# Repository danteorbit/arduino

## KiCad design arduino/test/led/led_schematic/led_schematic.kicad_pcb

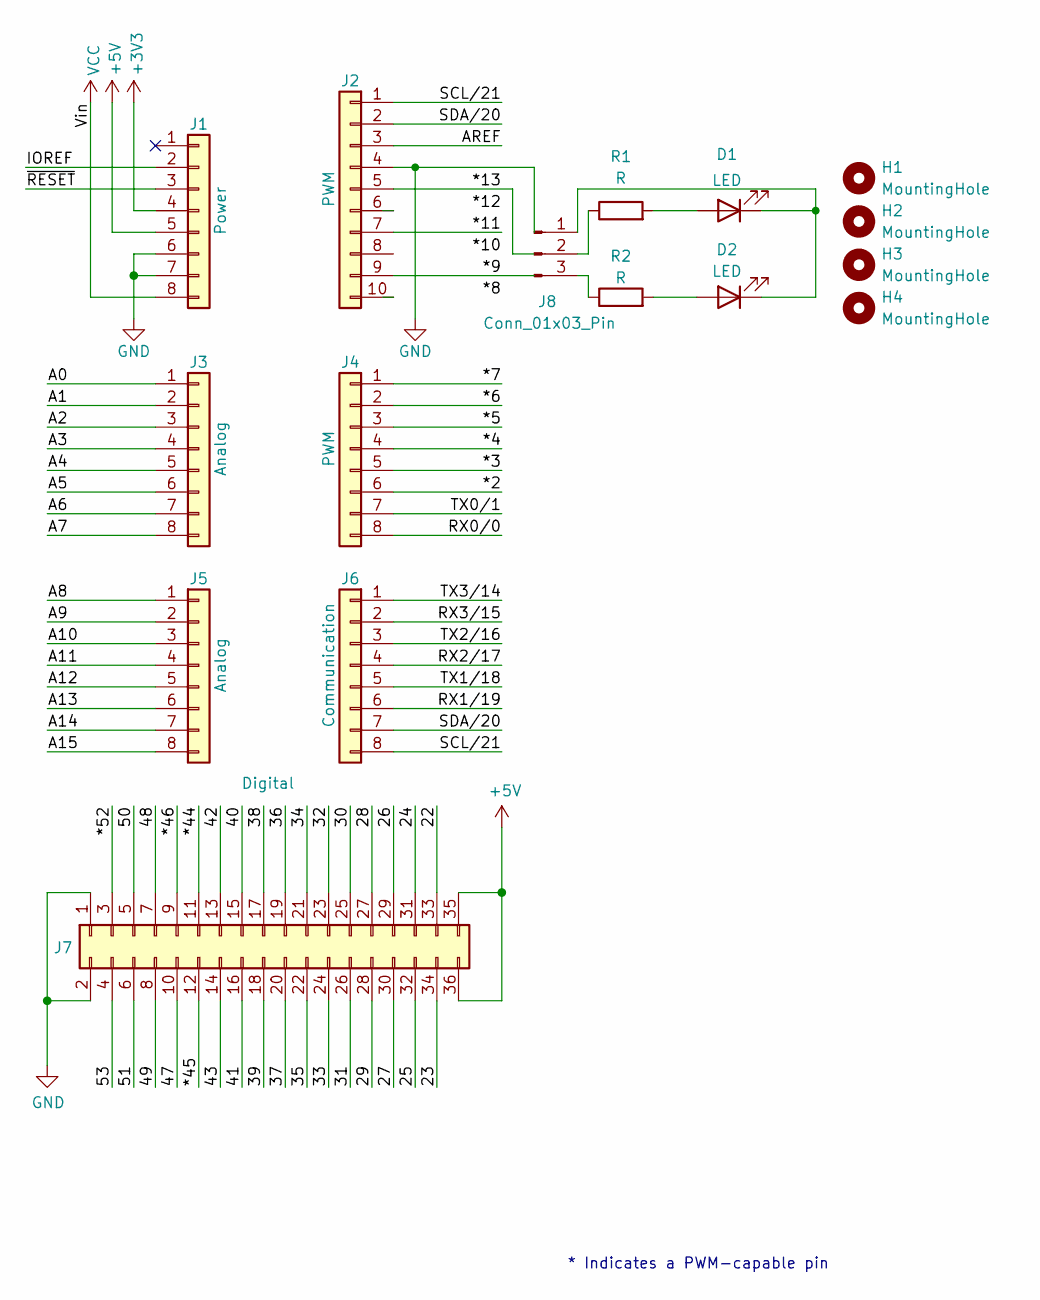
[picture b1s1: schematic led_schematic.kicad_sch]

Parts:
D1, D2: LED; LED_D3.0mm
H1, H2, H3, H4: MountingHole; MountingHole_1.2mm
J1: Power; PinSocket_1x08_P2.54mm_Vertical
J2: PWM; PinSocket_1x10_P2.54mm_Vertical
J3, J5: Analog; PinSocket_1x08_P2.54mm_Vertical
J4: PWM; PinSocket_1x08_P2.54mm_Vertical
J6: Communication; PinSocket_1x08_P2.54mm_Vertical
J7: Digital; PinSocket_2x18_P2.54mm_Vertical
J8: Conn_01x03_Pin; PinHeader_1x03_P2.54mm_Horizontal
R1, R2: R; R_Axial_DIN0204_L3.6mm_D1.6mm_P5.08mm_Horizontal

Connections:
+3V3: J1.4
+5V: J1.5, J7.35, J7.36
/22: J7.33
/23: J7.34
/24: J7.31
/25: J7.32
/26: J7.29
/27: J7.30
/28: J7.27
/29: J7.28
/30: J7.25
/31: J7.26
/32: J7.23
/33: J7.24
/34: J7.21
/35: J7.22
/36: J7.19
/37: J7.20
/38: J7.17
/39: J7.18
/40: J7.15
/41: J7.16
/42: J7.13
/43: J7.14
/47: J7.10
/48: J7.7
/49: J7.8
/50: J7.5
/51: J7.6
/53: J7.4
/*2: J4.6
/*3: J4.5
/*4: J4.4
/*5: J4.3
/*6: J4.2
/*7: J4.1
/*9: J2.9
/*11: J2.7
/*13: J2.5
/*44: J7.11
/*45: J7.12
/*46: J7.9
/*52: J7.3
/A0: J3.1
/A1: J3.2
/A2: J3.3
/A3: J3.4
/A4: J3.5
/A5: J3.6
/A6: J3.7
/A7: J3.8
/A8: J5.1
/A9: J5.2
/A10: J5.3
/A11: J5.4
/A12: J5.5
/A13: J5.6
/A14: J5.7
/A15: J5.8
/AREF: J2.3
/IOREF: J1.2
/RX0/0: J4.8
/RX1/19: J6.6
/RX2/17: J6.4
/RX3/15: J6.2
/SCL/21: J2.1, J6.8
/SDA/20: J2.2, J6.7
/TX0/1: J4.7
/TX1/18: J6.5
/TX2/16: J6.3
/TX3/14: J6.1
/~RESET: J1.3
GND: J1.6, J1.7, J2.4, J7.1, J7.2
unnamed: D1.2 (A), R1.2
unnamed: D1.1 (K), D2.1 (K), J8.1
unnamed: D2.2 (A), R2.2
unnamed: J8.2, R1.1
unnamed: J8.3, R2.1
VCC: J1.8

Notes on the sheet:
* Indicates a PWM-capable pin

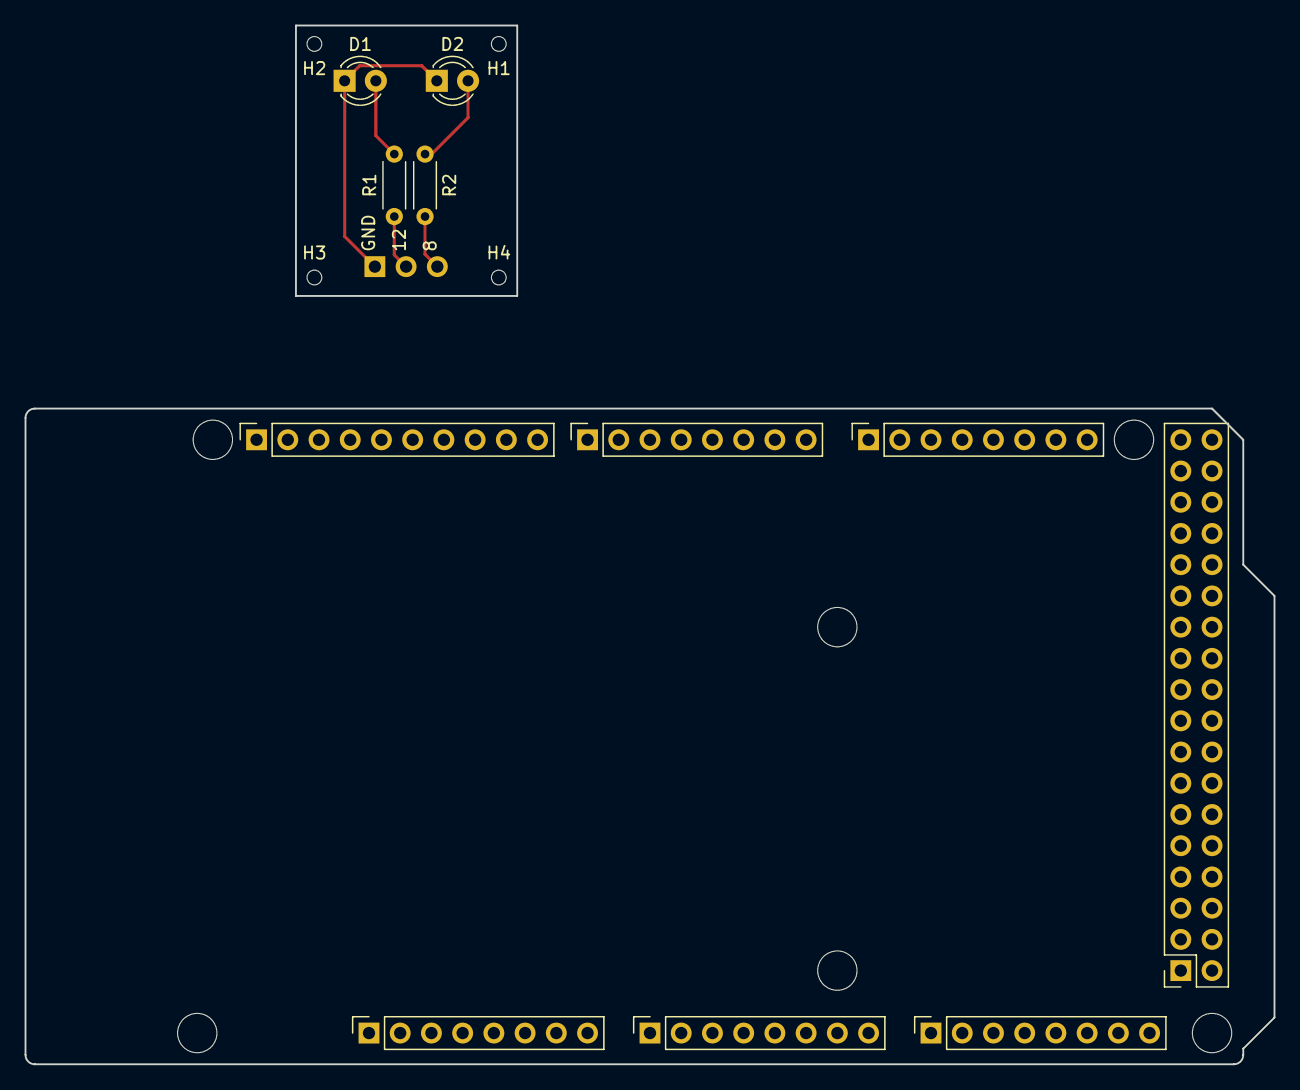
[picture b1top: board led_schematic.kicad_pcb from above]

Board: 2 copper layers, 101.6 x 84.5 mm, 22 parts (1 on the bottom side), 9 nets.

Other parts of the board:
MH1, MH2, MH3, MH4, MH5, MH6: MountingHole_3.2mm

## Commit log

2026-04-29 added led.cpp
2026-05-06 added ultrasonic.cpp
2026-05-06 added leds to ultrasonic sensor
2026-05-10 add led schematic
2026-05-10 updated .gitignore to ignore .history/
2026-05-10 added joystick modules
